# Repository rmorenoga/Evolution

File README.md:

# Evolution
Evolution of modular robots in different environments

The goal of this project is to evolve controllers for modular robots using evolutionary algorithms.

The Evolutionary framework used is JEAF (https://github.com/GII/JEAF) and the modular robots are simulated using V-REP(http://coppeliarobotics.com/).

## Setting Up

To set up the evolutionary system the simulation in V-REP and the Java Evolutionary framework (JEAF) should be downloaded and set up. This guide will concentrate on setting up the evolution on an Ubuntu 14.04 64 bit computer. This project uses java so a jre or jdk version 1.7 or newer should be installed on the pc. The whole project is set up as an Eclipse (https://eclipse.org/) project.

### MPJ

In order for the JEAF framework to work the mpj library should be installed, to do this first download it from the mpj-express project page http://mpj-express.org/download.php the mpj library comes in a compressed folder and can be put anywhere on the file system, we recommend to uncompress it in a folder under the /home/ folder (for example /home/username/MPJ/). The following lines should be added to the .bashrc file (for version 0.43 of mpj):

    export MPJ_HOME=/home/username/MPJ/mpj-v0_43
    export PATH=$MPJ_HOME/bin:$PATH

and they should go before the line that says:

    If not running interactively, don't do anything
    
After restarting the user session in Ubuntu MPJ should be ready to work.

### Simulator

The V-REP simulator can be downloaded at http://www.coppeliarobotics.com/downloads.html, for this project the Linux 64 bit Pro edu version is used. The simulator comes in a compressed file that can be put anywhere on the file system, we recommend to uncompress it under the /home/username/V-REP/ folder.

Several copies of the simulator can be created; to copy the simulator just copy all the files contained in the compressed file and put them on a different folder, for example copy them to /home/../V-REP/Vrep0/ and /home/../V-REP/Vrep1/. The numbering makes them easier to call later from the main evolutionary algorithms in java.

Three files should be modified inside the simulators files in order for them to run properly with this project, for example for the simulator in .../V-REP/Vrep0/ the files "vrep" and "vrep.sh" should be changed to "vrep0" and "vrep0.sh" respectively, also the field's "portIndex1_port" value inside the "remoteApiConnections.txt" file should be changed depending on the number of the simulator; for the simulator on ../Vrep0/ the value should be 19997, for ../Vrep1/ it should be 19996 (which is 19997-1) and so forth. 

### Simulation

The simulation scene files can be found in the Maze folder (/Simulation/Maze/).

The file MazeBuilder01.ttt contains all that is needed for the evolution of a robot with no sensors to take place. This file receives the parameters from the main evolutionary algorithms in java, builds a maze for the robot, runs the simulation and returns a fitness to the main algorithm, for it to work properly, the file should be opened with V-REP and the script associated with the InitControl object should be modified. 

Inside the InitControl object script are four lines that load the basic parts of the maze like this:

    shandle = simLoadModel("/home/.../V-REP/corridors/StraigthCorr.ttm")

and should be modified to reflect the location of the model files in the file system, the model files can be found inside the corridors folder under the Maze folder (/Simulation/Maze/).

### JEAF

The JEAF library jar files are already included under the VREPControl/lib folder and should be included in the path in order for the evolutionary algorithms to work. The simulator file "libremoteApiJava.so" should also be included in the program path to correctly communicate with the simulator. The "libremoteApiJava.so" file can be found in the folder /programming/remoteApiBindings/java/lib/64Bit in the simulator files.

### Evolutionary algortihm

The file:

/VREPControl/src/evolutionJEAFParallelRemote/EvolJEAFMazeR.java    (Main)

is an example of a main class for an evolutionary run. This class initiates the mpj parallel environment, starts the simulators as needed and the evolutionary process based on the parameters of the configuration file. The file should be modified to reflect the location of the simulators in the file system.

    qq.directory(new File("/home/.../V-REP/Vrep" + myRank + "/"));
    
and of the simulation scene file:

    ProcessBuilder qq = new ProcessBuilder(vrepcommand, "-h",
					"/home/.../Maze/MazeBuilder01.ttt");

 For this specific example the configuration file is required as a parameter of the program when executed from the command line. An example configuration file can be found in:

/VREPControl/EvolconfigMazeRS234.xml

The configuration file contains all the parameters needed for the evolutionary algorithm, from the population size, number of generations and type of evaluation to use, to the class that defines the fitness function. The fitness function is implemented in a class that extends the ObjectiveFunction class of the JEAF framework. For the configuration file example provided above the objective function class can be found on:

/VREPControl/src/evolutionJEAFParallelRemote/CalcFitnessMazeRS234.java

This class receives the parameters for the individual to be evaluated, packages and sends them to the corresponding simulator, and runs the robot simulation. When the simulation signals that is done the objective function class receives the results, calculates the fitness and returns it to the evolutionary process in JEAF. If there is an error during the simulation or the simulator stops responding this class also attempts to restart its corresponding simulator and tries again to evaluate the individual. In order to restart the simulator the location of the simulator should also be changed accordingly inside the RestartSim method:

    qq.directory(new File("/home/.../V-REP/Vrep" + myRank + "/"));
    
as well as the location of the scene file to simulate:

    qq = new ProcessBuilder(vrepcommand, "-h",
					"/home/.../Maze/MazeBuilder01.ttt");

### Running

In order to do an evolutionary run, all the files must be "compiled" (put in a jar file for our purposes) and all the libraries that it depends on should also be included in this jar file, this can be done by using Eclipse or any other tool. Once the jar file is generated the program can be run using the following command in a terminal:

    mpjrun.sh -np numberofprecesses -dev niodev -Djava.library.path=pathtojarfile -jar Jarfile.jar

provided that the configuration file and the "libremoteApiJava.so" file are inside the same folder as the jar file. The number of processes indicates the number of simulators that will be used at the same time, for example when using the above defined simulators, Vrep0 and Vrep1, this number will be 2.

Alternatively the program can be run from Eclipse by using an mpj-express plugin, the installation and basic usage of this plugin can be found on the following guide http://mpj-express.org/docs/guides/RunningandDebuggingMPJExpresswithEclipse.pdf All the necessary files and libraries should be included in the project path in order for it to run.

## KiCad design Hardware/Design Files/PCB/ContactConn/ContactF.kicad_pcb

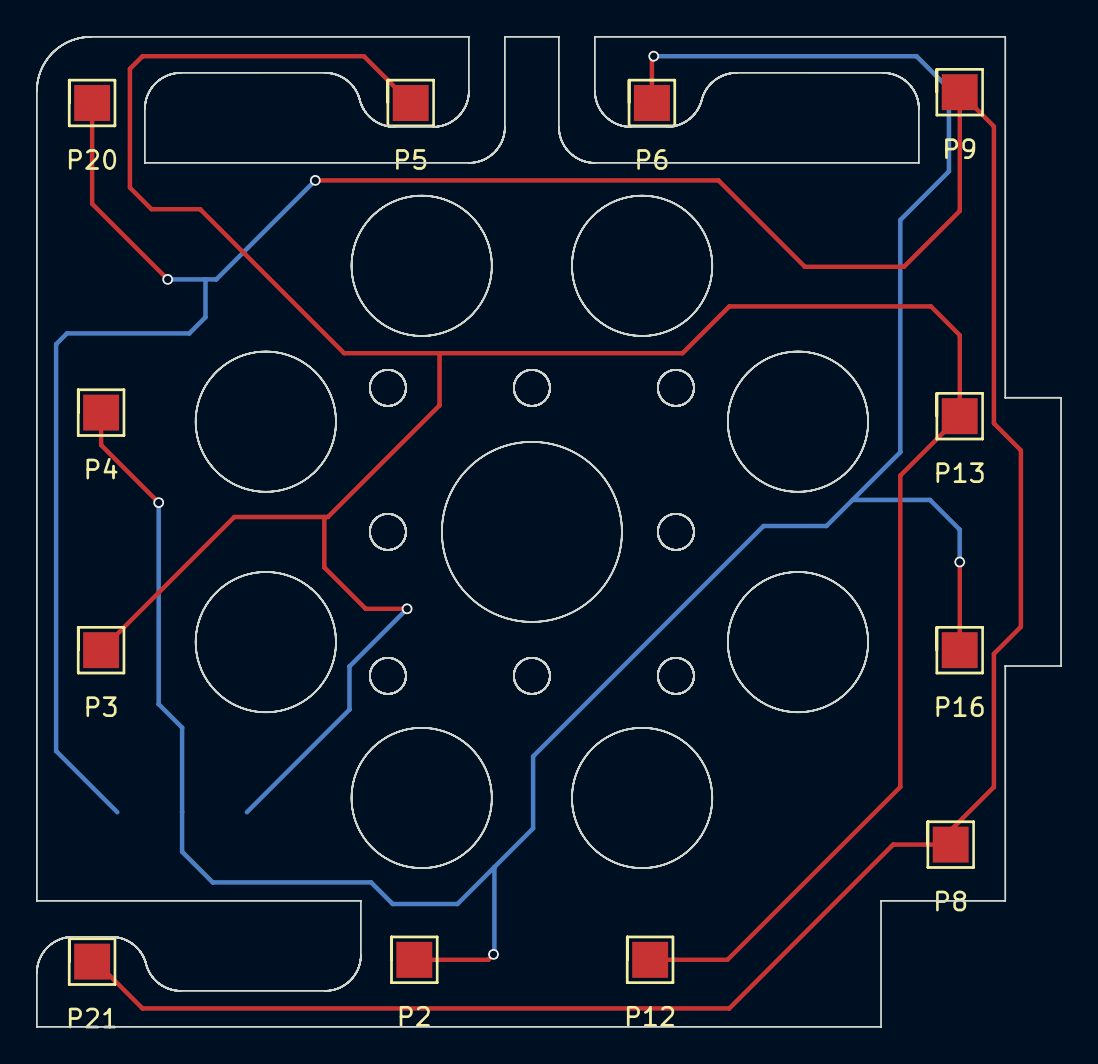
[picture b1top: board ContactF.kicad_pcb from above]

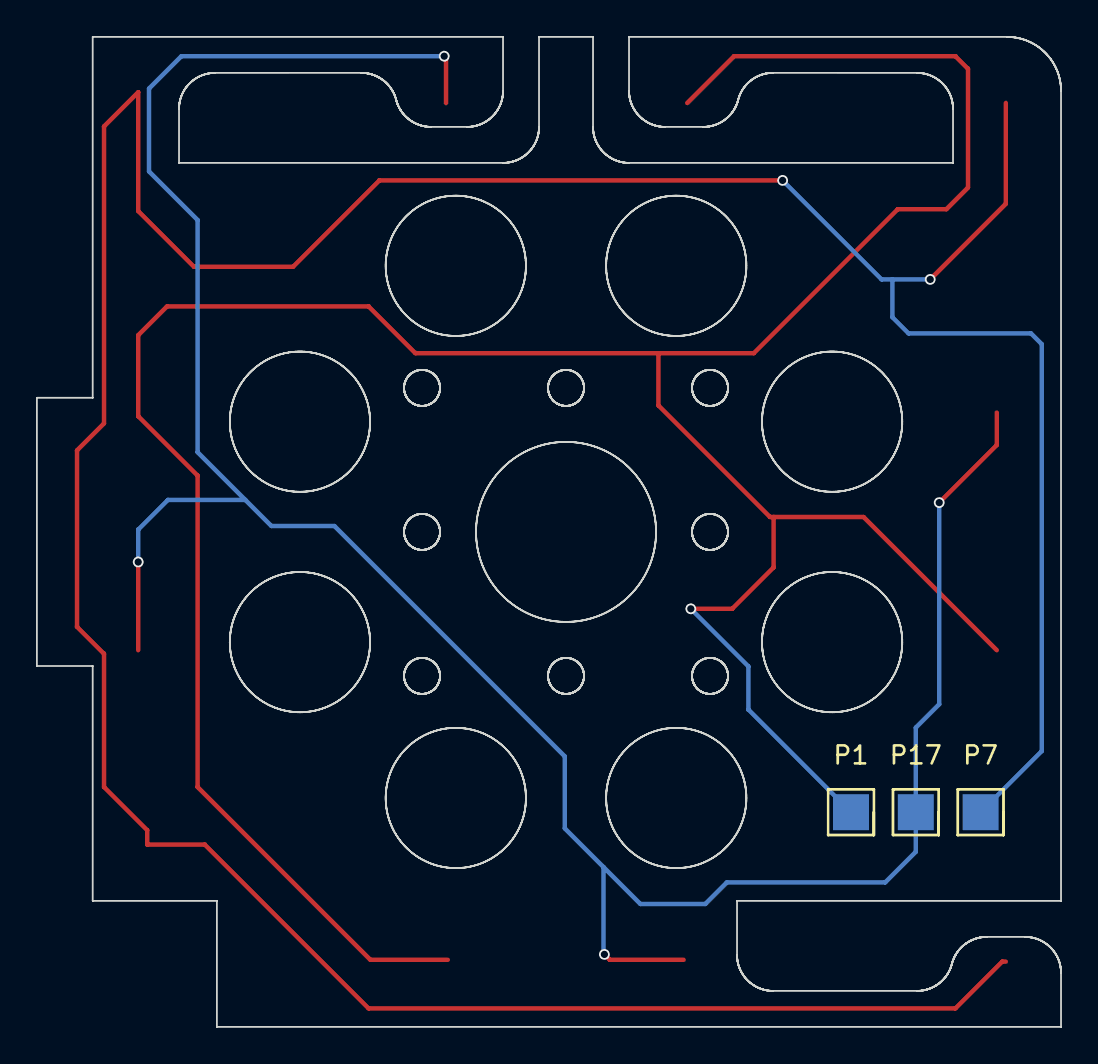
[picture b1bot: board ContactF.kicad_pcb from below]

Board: 2 copper layers, 56.9 x 55.0 mm, 15 parts (3 on the bottom side), 3 nets.

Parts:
P1, P2, P3, P4, P5, P6, P7, P8, P9, P12, P13, P16, P17, P20, P21: CONN_01X01; MYCONN2

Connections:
GND: P2.1, P4.1, P6.1, P16.1, P17.1
unnamed: P7.1, P8.1, P9.1, P20.1, P21.1
VCC: P1.1, P3.1, P5.1, P12.1, P13.1

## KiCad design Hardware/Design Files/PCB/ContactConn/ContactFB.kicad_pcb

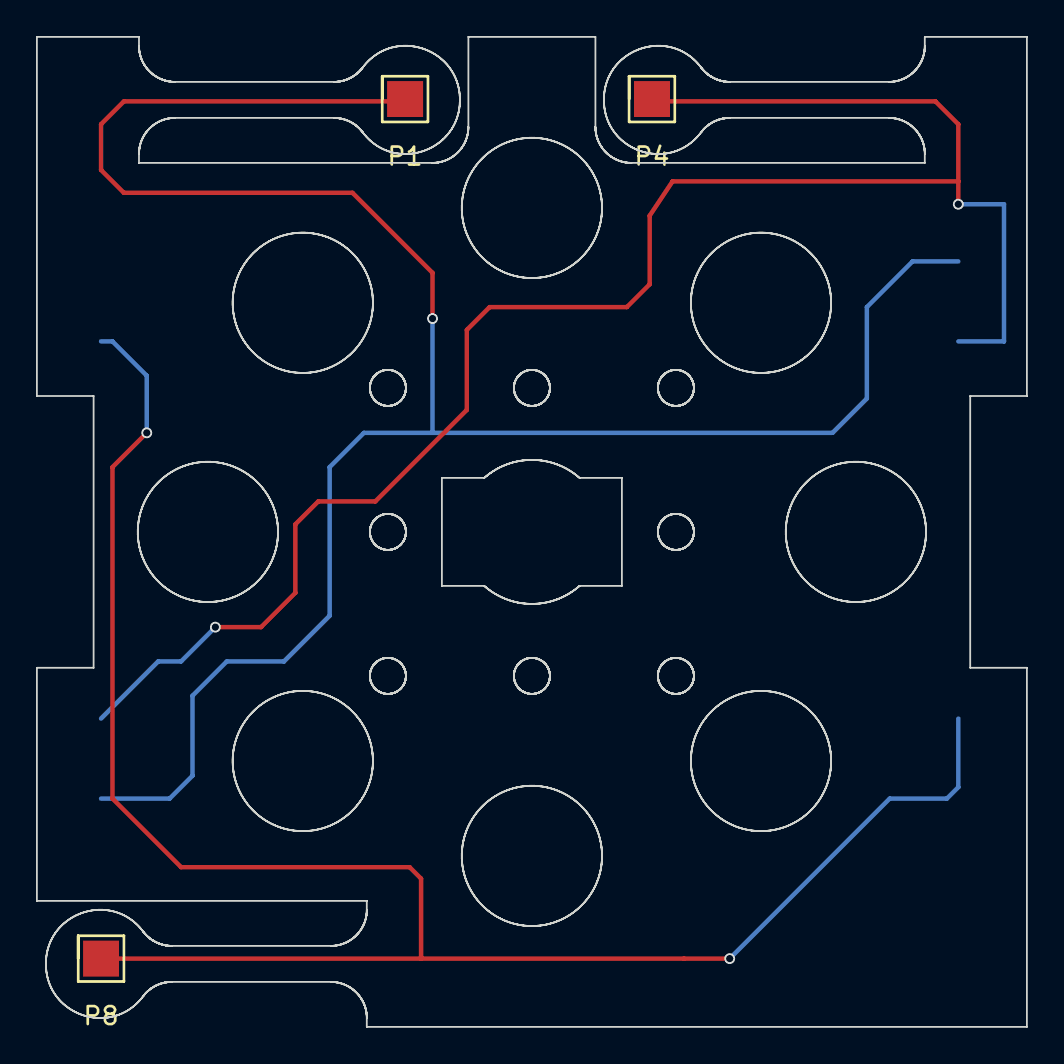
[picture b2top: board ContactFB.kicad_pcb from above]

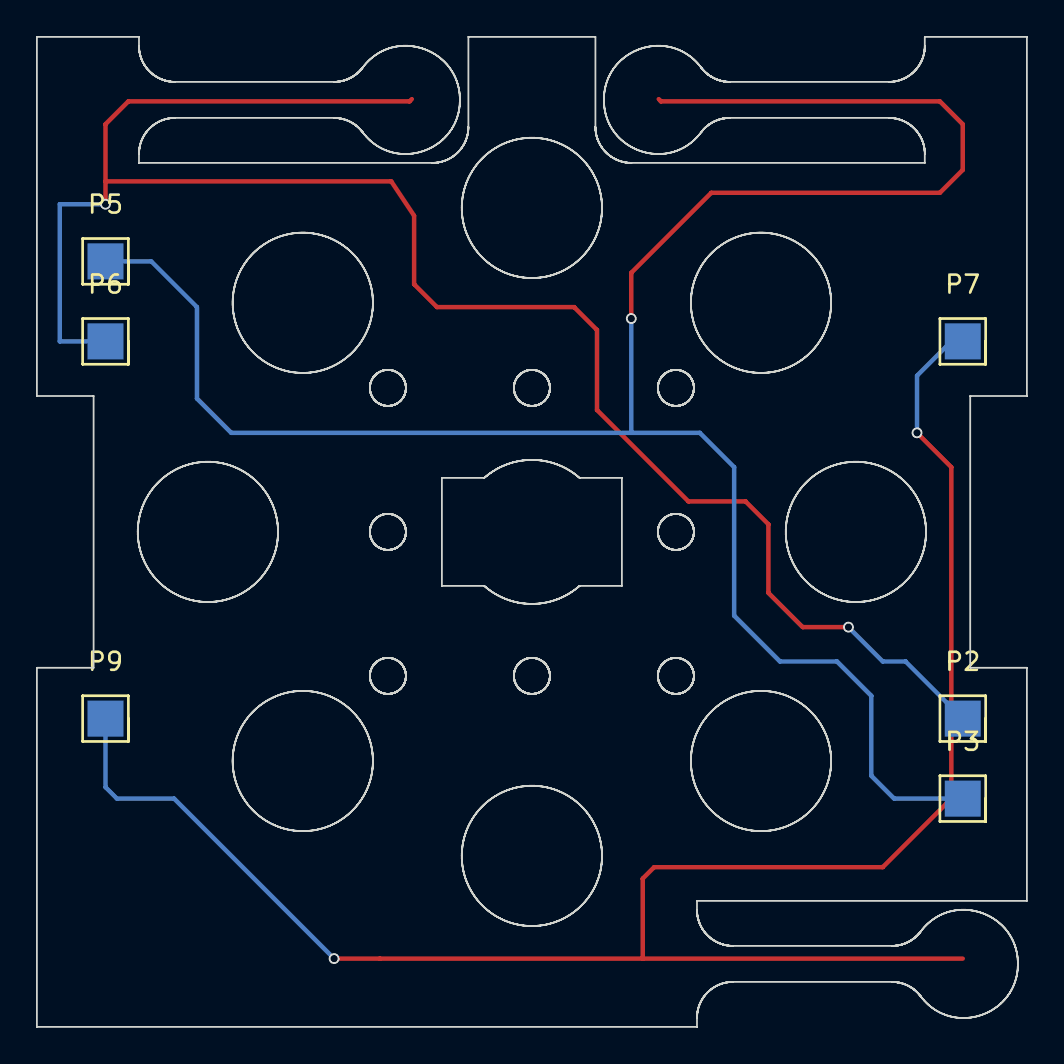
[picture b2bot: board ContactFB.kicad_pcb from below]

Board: 2 copper layers, 55.0 x 55.0 mm, 9 parts (6 on the bottom side), 3 nets.

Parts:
P1, P2, P3, P4, P5, P6, P7, P8, P9: CONN_01X01; MYCONN2

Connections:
GND: P2.1, P4.1, P6.1
unnamed: P7.1, P8.1, P9.1
VCC: P1.1, P3.1, P5.1

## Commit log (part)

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2015-05-20 First checkin with all files and gitignore
2015-05-26 Revert "Changed environments to run into Vrep with JEAF"
    This reverts commit 2d564964cb91481d3bb3fa47deab8a508f692304.
2015-05-26 Added a start number and xml file in arguments of main
    The programs now requires a start number to determine on which group of
    simulators it will start, a xml file for the algorithms configuration
    should also be specified this is to be able to use different objective
    functions with the same main.
    Fixed RestartSim and termination commands to only kill the corresponding
    simulator for each process
2015-05-31 Implemented use of average fitness after all subenvironments are solved
2015-06-20 Created class for evolving in a maze of 6 sub-environments
2015-09-08 Created README File
2015-09-16 Organized and comented some files
2015-09-16 Added running instructions on the readme
2015-10-07 Added hardware files in the repository
2015-10-14 Changed Readme.md to reflect new location of simulation files
2015-11-04 Changed introduction to Readme
2015-12-10 Added HillCLimbing package to test hillclimbing on the sub-environments problem
2016-03-17 Added a test class in the Tests package to send cpg parameters individually to an 8 module chain. Closed connection with the simulator in TimeTest.java. Created simvrep package and moved simulation c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
2016-03-18 Updated PCB and CAD files to reflect changes in the module connectors
2016-05-20 Created a quaternion to euler xyz conversion test class
2016-06-03 Corrected the array sending method to work correctly with the coppelia classes
2016-06-17 Fixed the Simulation class in simvrep to correctly interface simulator.
    MDebug scene implemented to test full communication and control from
    java when using the Simulation class and the new InitControl
    Customization and Child scripts that separate building of the maze and
    robot and the watchdog functionality accordingly.
2016-08-12 Testing pre-commit hook script
2016-08-12 Ditched pre-commit, using bash script instead.
    Commiting the real simulation files after pre-commit script fail.
2016-08-18 Created a run scene that doesn't print anything.
    Fixed the RestartSim method in the Simulation class
2016-08-22 Changed V-REP command to initialize it in headless mode
    It seems the no GUI compiled version of the simulator is not working
    well with the RemoteAPI
2016-09-19 Corrected V-rep simulation restart path
2016-09-29 Modified HAEAParallel to launch the simulators
2016-11-01 Put simulator start into a loop inside the script
2016-11-25 Implemented u+1 algorithm without ramdom movement in single robot
2016-12-02 Started testing plugins in v-rep for online evolution
2016-12-10 Started to create a central hub for all simulation experiments in java
2016-12-11 Added vrep files needed for robot building to work
2016-12-17 Implemented hormone generation, receptors and propagation in 4f model
2016-12-22 Created tree representation for robot and added handler information
2016-12-24 Created a robot controller factory to load controllers from xml
2016-12-29 Cleaned robot building reading from encoding and SimulationConfiguration
2016-12-31 Created JEAF evolution and objective function class to be xml controlled
2017-01-05 Tested JEAF parallel evaluation with multiple simulators
2017-01-20 Created a kind of selective differential evolution using JEAF
2017-03-07 Fixed MRun.ttt to run single threaded evaluations
2017-03-16 Set up tracer for HAEAS
2017-03-29 Fixed simulation control for parallel evaluation in HAEA.
    Limited the scope of the controlled simulator in HDebugP to the apply
    method, this prevents one apply in one thread to mistakenly control the
    simulator in the other thread.
2017-03-31 Corrected bugs in favor module simulation.
2017-04-04 Made HDebugP configurable with robot parameters
2017-04-07 Fixed descriptors in HAEAParallel
    This lets the first iteration to be evaluated by all available
    simulators
2017-04-28 Modified favorfirst to accept extra parameters in the beginning.
    Modified MHormFI to accept an extra delta parameter for adjusting
    inlfuence of the hormone messages
2017-05-01 Started creating evaluator class to use emerge module with HAEA m-thread
2017-05-03 Modified CPGH emerge module to accept extra parameters.
    Horm.lua now randomly generates the base hormone with a set probability
2017-05-03 Modified CPGH and CPGHF controllers to accept 3 extra parameters.
2017-05-17 Included script for copying simulation files in rmorenoga
2017-05-23 Commented chromo creation process in Em module ShowHFitReal.
    Now we can design robots manually by modifying the chromo code directly
2017-06-02 Implemented random sequence with average maze in HEmP.
2017-06-08 Organized Favor and non favor operators in HAEAParallel
2017-06-16 Fixed communication problem in CPG Emerge modules.
    Fixed bug that didn't allow RobotController adjustParameter method to
    handle CPG controllers
2017-07-30 Changed logger function to create a new line/object for every time step
    Log files should now be streamed into R with stream_in function
    Moved log function to the beginning of the actuation part of the
    simulation to get information of first time steps
2017-08-03 Found that adjustextraparam was distorting delta value for controllers.
    Checked that hormone system was working as intended with small delta
    value.
    Extra caution should be used when using extra parameters in the
    evolutionary runs.
    Added logCPG to logger.lua to track actual CPG values in CPGHLog.
2017-08-04 Created smaller versions of corridors for EMERGE module
2017-08-10 Adjusted Maze.lua to accommodate short corridors
2017-08-11 Verified behavior of ParamMask with ShowHFitReal and HAEAParallel
2017-08-16 Implemented broken force sensor stop condition on defaultmhs
    Tested CPGSingle parameter mask in its two modes
2017-08-17 Modified DEXover to accept only different individuals as parents
    Should be used with NUniqueIndividuals as selection in HAEA
2017-08-18 Created class for masking parameters to CPGH controllers.
    CPGHSingle masks a set of parameters for one module to all modules in
    the morphology
2017-08-21 Collapsed Subparammask, SubCPGHS and CPGHSBase into single class
2017-08-23 CPGSingle now changes the sign of phasediff in case of snake morph.
    defualtmhs is now back tracking in its original direction, width is
    fixed
2017-09-01 Added xvfb functionality to simulator launch
2017-10-01 Changed probabilistic propagation to attenuation in CPGH and CPGHLog
2017-10-04 Each robot node able to discover its connected modules orientations.
    RobotTree returns a list of connected orientations from all nodes.
2017-10-06 Defined transformation dictionary in Spatial for current robotbuilder
2017-10-09 Compartmentalized spatial functions
2017-10-12 Implemented orientation based hormone generation
2017-10-15 Separated spatial transformation from receptors and propagate processes
2017-10-26 Introduced ANNBasic receptors model stud in Horm and ReceptorsH
2017-10-29 Verified inputs and outputs in receptorsANN. Tested with trained ANN.
2017-10-31 Configured JEAF evol for ANNBasic controller
2017-11-01 Created mask and interface stud for sending ori information to simulator
2017-11-16 Broken robot fitness is now D*1.5
2017-11-22 Configured HAEAParallel to run with CPGHANN
2017-12-05 Organized logger model CPGHLog for logging with new model
2017-12-06 Configured ANNBasic with 4 phases
2017-12-15 Created filter for hormsum in receptors.
    The filter has a window for adjusting how many simulation steps it will
    sum over to obtain the overall sum
2017-12-27 Created HillClimbingTest with bugs
2017-12-29 Modified HEmP for tracer to write best individual in hillclimbing
2018-04-04 Added parameters to HillClimbTest for doing different batches.
    Added TurnRight and SimpleBump case to HEmP
2018-04-04 Modified GeneralizationTest to read a folder containing result files
2018-04-10 Corrected Bug in CPGANN which fixed the parameters for any ANN
2018-04-14 Replaced Euclidean distance for manhattan distance in fitness measure
    Created HyperCubeFromPoint to generate a custom initial population by
    specifying a set of known individuals
2018-04-16 Tested and corrected bugs with BumpStepVWs
2018-04-17 Different fitness measures can now be switched from java in EvaluatorMT
2018-04-18 Corrected bug in incrementing fitness measure
2018-04-24 Created very basic controller for initial population snake
2018-05-02 Uisng PowerLawMutation instead of gaussian mutation, rate elevated
2018-05-03 Connected annInputSwitch with CPGH ann receptors
2018-05-04 Added JSON logger support for MixedGenome
2018-05-15 Random width and height in HEmP Generalization Test
2018-05-15 Extended MixedSpace to only evolve annWeights
2018-05-17 distPercent is sent from java. Handling in Maze(NOT WORKING YET)
2018-05-18 Configured short challenges in HEmP
2018-05-20 Deleted all mixedGenome configurations in evolHAEA
2018-05-20 Created class for holding multiple mazes and selecting one
    SelectableMaze also sets noisy dimensions to the maze around the
    original width and height through nextNoisyDimensions
2018-05-21 Verified working clean code
    Changed MaxTime signal to float
2018-05-28 Configured GenerationalEnvEmP in HAEAEmP and tested for bugs
2018-05-30 Fixed bug in HAEAEmP that prevented iteration information printing
2018-05-31 Configured ReadTXTFiles in GeneralizationTest
2018-06-07 Implemented getGoalFromFraction for l and r shapes
2018-06-21 Fixed bug that prevented nonStationary reevaluation
2018-07-24 Configured HAEAEmP for second morphology. EmP now registers iteration
2018-08-25 Set up IncrementalShortChallenge for test
2018-09-01 Tested IncrementalShortChallenge for bugs changed single EmP single eval
2018-09-16 Added challenge to test name in IncrementalShortChallenge
2018-09-18 ShortChallengeSettings now uses distance from start
2018-09-20 Fixed bug: incremental repli started with the last replica lastpop
2018-09-20 Added the initial s environment to incremental experiments
2018-09-21 Branch is overridden with latest master code
2018-09-21 Refactor: Created method for running linked challenges
2018-09-22 Setup for running bump seeds
2018-09-24 Added 10 seeds to seedPopStep
2018-10-04 Fixed bug that prevented the simulator from restarting after long time
2018-10-24 Added rhormnew parameter to logProp in CPGHLog
2018-10-27 Fixed bug that prevented an unordered simulator to be released in EmP
    An unordered simulator refers to a simulator which name number did not
    correspond to its number in the servers ArrayList
2018-11-07 Fixed Bugs in Evaluators
2018-11-10 Configured ReadJsonFile in LogIndividual to read different tests
2018-12-05 Added logger functions for filtered hormones and ANN inputs
2019-01-24 Change emerge module max torque in CPGH and CPG.
    Old settings are in strongemergeModule
2019-01-25 Configured hardware pre-evolution with 3 modules
2019-01-26 Created simple HAEA class for hardware experiments
2019-01-27 Set up working HAEA with json logging for hardware evolution.
    Replaced HAEA jars, right now incompatible with emst (multithread), DO
    NOT MERGE WITH MASTER BRANCH!!!
2019-02-02 Corrected fitness function and run first evolution in hardware
2019-02-03 SRand3 sets a random environment per generation
2019-02-04 updateCurrentEnv now checks for valid files
2019-02-06 Corrected tracing in HillTest
2019-02-13 Set up for evolution
2019-03-01 Set up for one combination test
2019-03-08 Set up HAEAEmp for running with coordinated seeds
